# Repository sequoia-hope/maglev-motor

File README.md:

# Planar Maglev Motor Simulator

A browser-based design explorer and 6-DOF flight simulator for **moving-magnet
planar motors**: a Halbach permanent-magnet platen levitating over a stationary
array of ironless coils.

No build step, no dependencies. Serve the directory and open `index.html`:

```sh
python3 serve.py 8000           # then http://localhost:8000  (no-store headers; see the file)
```

It is also published as a static site from `main` by GitHub Pages:
<https://sequoia-hope.github.io/maglev-motor/>. Everything is relative paths and
pre-rendered files, so the Pages copy has every tab and both link-outs: the **Board
report** (`route/report/`) and **Pcbview** (copper, 3D and parts in `route/pcbview/`,
built from `route/pcbview.toml`).

Tests (Node 18+, no dependencies):

```sh
cd test && node physics.test.mjs && node flight.test.mjs && node optimise.test.mjs
```

---

## What it models

The whole machine reduces to one object: a **6×N wrench matrix** `W`.

```
[Fx Fy Fz Tx Ty Tz]ᵀ  =  W(pose) · i
```

Column *j* is the force and torque produced by one ampere in coil *j*. Because
that relationship is exactly linear, everything else falls out of it:

| Question | Answer |
|---|---|
| What currents do I command? | `i = W⁺w` — damped least-norm commutation |
| How much force can it make? | singular values of `W` |
| Are there dead spots? | poses where σ<sub>min</sub>(`W`) collapses |
| How hot does it get? | `Σ iⱼ²Rⱼ` |
| Will it fly? | integrate a rigid body driven by `W·i` |
| How few amplifiers can I get away with? | `W_eff = W·G` for a grouping `G` |
| What should I actually build? | constrained search over the coupled design space |

### The field model

The platen magnetisation is expanded as a 2-D Fourier series over one spatial
period. For each harmonic with in-plane wavevector **k**, the field below a slab
of thickness *D* is

```
Bz(k) = ½(1 − e^(−kD)) · [ M̂z − i(kx·M̂x + ky·M̂y)/k ] · e^(−kd)
Bx(k) = i(kx/k)·Bz(k)        By(k) = i(ky/k)·Bz(k)
```

with magnetisation in tesla (`|m| = Br`). The bracket **vanishes for the
wrong-handed harmonic** — the Halbach one-sided-flux condition is a consequence
of the algebra, not an assumption. `orientStrongSideDown()` measures which face
the flux exits and flips the array if needed, so new patterns can't be silently
built upside-down.

The exact Fourier coefficient of the piecewise-constant magnet cells carries a
sinc factor, which is where the classic discrete-Halbach amplitude penalty
`sin(π/M)/(π/M)` comes from — it is derived, not hardcoded.

Force and torque come from Lorentz integration of `I·dl × B` over every coil
filament, negated by Newton's third law.

### Phase grouping

Real machines do not give every coil its own current source. Coils are wired or
switched into a few phase groups and commutated against the magnet phase —
Zhu/Teo/Pang drive ~120 live coils from **eight** amplifiers. Model it as a
linear map `i = G·u` from phase currents to coil currents, and the wrench matrix
simply composes:

```
w = W·i = (W·G)·u
```

so allocation, singular values and dead-spot maps all work on `W_eff` unchanged
(`test/physics.test.mjs` checks `W_eff = W·G` is exact to 4e-16). `G` holds
sinusoidal commutation weights over spatial regions that subdivide each magnet
array and follow the platen — the physically realisable kind. What it costs:

| Preset | Drive | Amplifiers | Cond. | 6-DOF? | Hover | Tracking |
|---|---|---|---|---|---|---|
| PCB | independent | 144 | 2.6 | yes | 7.5 W | 42 µm |
| PCB | 2×2 per array | **16** | 5.6 | yes | 11.4 W | 42 µm |
| Wound (cross) | independent | 121 | 2.5 | yes | 38.6 W | 66 µm |
| Wound (cross) | 1 per array | **8** | 3.0 | yes | 72.8 W | 66 µm |
| Racetrack | independent | 108 | 6.2 | yes | 38.6 W | 206 µm |
| Racetrack | 3×3 per array | 36 | 20.4 | yes | 60.4 W | *worst-case lift 0.98×* |

The headline: **8 amplifiers track exactly as well as 121** on the four-array
cross, at roughly double the hover power. That is the published design, and the
model reproduces it. The racetrack is the exception — see limitations below.

### Reading the machine view

Every part is drawn as an extruded solid with its real thickness — magnet
stack, winding build height, backing plate — because those thicknesses *are*
the design. Two viewing aids, both of which distort the picture deliberately
and label themselves on the canvas when active:

- **Section cut** along x or y, with a draggable plane. Hides everything past
  the cut so you can see the layer stack and the air gap in cross-section.
- **Vertical exaggeration** (z×1–12). A 1.5 mm air gap under a 72 mm platen is
  otherwise a sub-pixel sliver.

The air gap carries a live dimension callout, since it is the variable
everything else trades against. The backing plate is drawn translucent so the
magnet array stays visible at true scale.

### The mechanical stack

Three numbers used to be invented: platen mass was `magnetMass × 1.6`, the
air-gap floor was `1.5% of platen size`, and cooling was a fixed
`h = 12 W/m²K`. `src/mechanical.js` replaces all three with parts that have a
material, a thickness and a manufacturing process.

**The air gap is now a tolerance stack**, not a guess:

```
gap_min = stator flatness + platen flatness + coil height variation
        + magnet thickness tolerance + thermal expansion
        + control error + safety margin
```

Every term is traceable. Flatness comes from the *process* — CNC ≈ 0.05 mm per
100 mm, PCB laminate ≈ 0.75% of diagonal per IPC-6012 — and it scales with part
size, so a bigger machine is a flatter machine only if you pay for it. On the
PCB preset, board flatness alone is 0.72 mm of a 1.32 mm floor: it is not a
contributor, it *is* the budget.

**The loop closes back on the simulator.** One term is the closed-loop control
error, which the flight sim measures. "Use measured error" on the Simulate tab
feeds the observed worst-case vertical excursion into the budget — because you
cannot fly closer to the stator than you can hold position. Quiet hover reads
sub-micron; kick the platen at 0.6 g and the peak excursion is **702 µm**,
which pushes the PCB preset's floor from 1.32 mm to **2.11 mm** — past the
1.5 mm gap it was designed around. Disturbance rejection and mechanical
clearance are the same budget, and this is the only way to see that.

It also prices things that were previously free. The magnet retainer wall
displaces 25% of the magnet layer on the PCB preset — that is field you do not
get — and adjacent Halbach magnets push about 15 N apart, which is what the
retainer wall has to survive during assembly.

### Design search

A 1-D sweep answers "what is the best pole pitch, holding everything else
fixed?" — the wrong question, because the optimum pitch depends on the air gap,
which depends on the winding height, which trades against turn count. The
**Optimise** tab searches them together: random sampling to find the basins, then
pattern search from the best candidates. ~330 designs/second, so a 500-design
search takes under two seconds and runs in animation frames without blocking.

Designs are **constrained, then ranked** — never a weighted sum of objectives. A
weighted sum silently trades a hard physical requirement for a soft one, and no
amount of low hover power compensates for a machine that cannot lift itself
somewhere in its workspace. Hard gates: worst-case lift, stator ΔT, current
density, amplifier count, full rank-6 controllability, and a buildable air-gap
floor. Then one objective (max acceleration, min power, max lift-per-watt, …).

Any result can be pushed back into the live config — from the best-design card,
a table row, or by clicking a point in the design-space scatter. Applying
**re-verifies at full solver quality**, since the search runs coarse; the two
agree to ~3%.

**Pin what you already know.** With ten coupled variables you usually know
several of them from the application — the platen has to be 120 mm, the gap has
to clear a 2 mm contamination budget — and want the budget spent on the rest.
Untick a dimension and it is held at the value shown, editable right there
(edits flow straight into the live design). Ticked dimensions get an editable
min/max, so you can also just narrow a range rather than pin it outright. The
panel reports how many of the variables are actually being searched.

Three things the search does that a sweep cannot:

- **Reports which bounds are binding.** If the winner sits on a search bound,
  the bound chose the value, not the physics, and it says so.
- **Reports why nothing was feasible.** A ranked histogram of which constraint
  blocked how many candidates — the top row is the one to loosen.
- **Shows the Pareto front**, so you can see the trade rather than just the
  single point that happened to win the objective you picked.

It also validates itself: given free rein over the coil-pitch ratio, the search
independently converges on **λ/3** — the three-phase spacing the literature
prescribes, and which this simulator earlier had to discover the hard way.

Run against the PCB preset it found, in ~350 designs, a machine strictly better
on every axis than the hand-tuned starting point:

| | hand-tuned | searched |
|---|---|---|
| Lift margin | 4.73× | **9.37×** |
| Lateral accel | 4.96 g | **6.8 g** |
| Hover power | 11.4 W | **4.71 W** |
| Stator ΔT | 51 K | **9.5 K** |
| Amplifiers | 16 | 16 |

### Validation

`test/physics.test.mjs` checks the model against independent ground truth:

- fundamental amplitude vs the closed form `Br(1−e^(−kD))·sin(π/M)/(π/M)`, for
  M = 2, 3, 4, 6, 8 — **exact to 0.00%**
- wrong-handed array's flux suppressed to 5×10⁻¹⁷ T
- field decay constant equals `2π/λ` to 1 part in 10⁶
- **lift capability of the assembled machine falls off at the harmonic decay
  rate** `k = 2π√2/λ` — an end-to-end check through geometry, Fourier
  decomposition, Lorentz integration and the allocator
- allocation linearity, pure-lift orthogonality, rank-6 controllability

The same fundamental check runs live in the sidebar. **If it says FAIL, nothing
else on screen is trustworthy.**

`test/flight.test.mjs` flies every preset through hover, circle and raster
trajectories and asserts it stays airborne and settles.

---

## Things the simulator taught us

These were found *by* the tool during development, and are the kind of thing it
exists to surface:

- **Coil pitch = λ/2 is a trap.** The coil grid lands exactly in phase with the
  magnet array and lateral force cancels *identically* at symmetric poses — a
  50× collapse in thrust while lift looks perfect. This is why three-phase
  designs use λ/3. The capability map shows it immediately.
- **Full-width racetrack coils cannot control yaw.** Force is uniform along each
  coil's length, so no current distribution produces T<sub>z</sub> and `W` drops
  to rank 5. Real racetrack stators are built as blocks of finite-length coils
  for exactly this reason.
- **There is an optimum pole pitch.** Run the pole-pitch sweep: lift margin
  peaks and hover power bottoms out at a specific λ for a given air gap. Too
  fine and the field never reaches the coils; too coarse and you waste magnet.
- **Saturation must prioritise levitation.** Scaling the whole commanded wrench
  back when the drivers run out throttles lift too, and the platen falls.
  `allocatePrioritised()` solves lift first and spends the remaining headroom on
  manoeuvring.
- **Turn count is not a free parameter.** Coil turns are derived from
  `(window area × 0.7) / wire area`. Allowing a turn count to be typed in
  produced a "12 mm" coil that would physically stand 96 mm tall and reported a
  lift margin it could never deliver — 56 kg of copper in a stator meant to lift
  1.7 kg.
- **Lift capability depends only on current density, not wire gauge.** Since
  turns × wire-area is fixed by the window, `lift ∝ N·I ∝ J`. Choosing thicker
  wire buys nothing but fewer turns. This is why the current-density tile, not
  the ampere limit, is the number that decides whether a design needs cooling.
- **Segmented racetrack coils need staggering.** Un-staggered, every coil in a
  column ends at the same y, so the platen periodically straddles a seam where
  only perpendicular end-turns sit beneath it. Lift collapsed to **0.16×
  weight** in bands a few mm wide — the platen fell straight through them.
  Staggering alternate columns by half a segment took worst-case lift from 0.16×
  to 1.44×.
- **Grouping is nearly free on the right layout, and impossible on the wrong
  one.** Eight amplifiers match 121 on the four-array cross; the racetrack loses
  so much capability that worst-case lift falls below 1× weight. Which topology
  you pick determines whether you need 8 drivers or 108.
- **A radial four-array cross has no yaw authority at all.** Each array at
  position `r` thrusting along `r` contributes `r × F = 0`. The arrays must
  thrust *tangentially*. This bug was invisible under per-coil control (single
  coils can still make yaw) and only surfaced once array-level grouping forced
  the layout's structure to matter — fixing it also improved independent-drive
  conditioning from 5.1 to 2.5.
- **Never judge a stator at its centred pose.** That pose is a symmetry point.
  `flight.test.mjs` now sweeps a ±30 mm workspace and demands the design hover
  *everywhere*; the racetrack dead bands were invisible to a centred check.

## Layout

```
index.html          Design (static analysis), Optimise (search), Simulate (flight)
src/math.js         vectors, quaternions, Cholesky, Jacobi eigenvalues
src/halbach.js      magnet tiles, Fourier decomposition, air-gap field
src/coils.js        stator topologies reduced to current filaments
src/physics.js      wrench matrix, allocation, rigid-body dynamics
src/control.js      6-DOF PID with gravity + acceleration feedforward, trajectories
src/analysis.js     design sweeps (gap, pole pitch, capability maps, ripple)
src/grouping.js     phase grouping: commutating many coils from few amplifiers
src/optimise.js     constrained multi-dimensional design search
src/mechanical.js   stack-up: masses, tolerance budget, thermal path
src/render3d.js     dependency-free solid-geometry 3-D canvas renderer
src/plots.js        line charts, heatmaps, bar strips with hover readouts
src/app.js          parameter UI, presets, the frame loop
```

## Known approximations

- **Finite array edges** use a half-pitch smooth taper on the periodic field.
  Errors are largest within about one pole pitch of an array edge; a truly
  finite array needs a surface-charge model.
- **No eddy currents, no iron, no back-EMF limit.** The current source is ideal;
  real drivers run out of voltage at speed.
- **Thermal estimate is crude** — a fixed natural-convection coefficient over
  the stator footprint. It flags designs that will obviously melt; it does not
  size a heatsink.
- **Magnet μ<sub>r</sub> = 1** (real NdFeB ≈ 1.05).
- **Winding packing is a flat 0.7**, reasonable for layer winding, optimistic
  for a hand-wound scramble winding (~0.5).
- **Commutation weights are sampled at each coil's centre.** Accurate for
  compact coils (square, PCB spiral), poor for long racetracks whose two long
  sides span a wide range of magnet phase. Some of the racetrack's poor
  behaviour under grouping is this approximation rather than the topology.
- **The search optimises the model, not reality.** Every approximation above is
  inherited, and an optimiser is extremely good at finding whichever corner of
  the model is least faithful. Treat a searched design as a hypothesis to check,
  not an answer — and read the active-bounds warning first.
- **Plate stiffness is not modelled.** Flatness comes from the manufacturing
  process, not from a deflection calculation, so a platen that is too thin to
  hold its own shape will not be caught.
- **Magnet-to-magnet force is an order-of-magnitude bound** (`B²/2µ₀` over the
  facing area). Real Halbach neighbours meet at 90°, so the load is largely
  shear and the true figure is lower.
- **No driver electrical model.** Amplifier count is reported, but voltage
  limits, back-EMF and the switching matrix itself are not simulated.
- The wrench matrix is rebuilt at the control rate, not every dynamics substep.

## Source literature

- W.-J. Kim, *High-Precision Planar Magnetic Levitation*, PhD thesis, MIT, 1997 —
  [dspace.mit.edu](https://dspace.mit.edu/handle/1721.1/10419). Where the field
  started: four Halbach linear levitation motors under one 5 kg platen.
- J. W. Jansen, *Magnetically Levitated Planar Actuator with Moving Magnets*,
  PhD thesis, TU Eindhoven, 2007 —
  [PDF](https://pure.tue.nl/ws/files/2471953/200711951.pdf). The harmonic
  force/torque model implemented here, plus commutation and decoupling.
- H. Zhu, T. J. Teo, C. K. Pang, *Design and Modeling of a Six-Degree-of-Freedom
  Magnetically Levitated Positioner Using Square Coils and 1-D Halbach Arrays*,
  IEEE Trans. Industrial Electronics 64(1):440–450, 2017 —
  [PDF](https://danielteodesigntechnology.wordpress.com/wp-content/uploads/2011/06/maglev_square_coils_tie2016.pdf).
  The most buildable topology.
- *Force and Torque Model of a Magnetically Levitated System with 2D Halbach
  Array and PCB Coils*, Sensors 23(21), 2023 —
  [open access](https://www.mdpi.com/1424-8220/23/21/8735). Tileable 16-layer
  PCB stator.
- *FleXstage*, arXiv 2309.11735 — [PDF](https://arxiv.org/pdf/2309.11735).
  Over-actuated lightweight platen.
- R. Chen, *A New Type of Magnet Array for Planar Motor*, MSc, UBC —
  [PDF](https://open.library.ubc.ca/media/stream/pdf/24/1.0340572/3). Array
  topologies with gaps and staggers.

Commercially this is [Planar Motor Inc.](https://planarmotor.com/) (UBC spinout)
and Beckhoff XPlanar — both moving-magnet 2-D Halbach over coil tiles.

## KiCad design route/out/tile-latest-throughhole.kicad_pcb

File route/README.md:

# Routing the amzhex coil board

A toolchain that takes the `amzhex` preset from the simulator to a real,
autorouted `.kicad_pcb` and checks it against JLCPCB's published 12-layer
capabilities. Everything here is a thin driver around `src/kicad.js` — the board
itself is still generated by the same code the app and the tests use.

```
gen.mjs      preset  ->  amzhex.kicad_pcb        (the real 12-layer board)
route.mjs    board   ->  amzhex.route.dsn        (the routing problem, see below)
freerouting  dsn     ->  amzhex.route.ses
finish.sh    ses     ->  out/*.kicad_pcb + DRC + PNG
```

Every step is reproducible from the one before it, and that is a property worth
keeping: `gen.mjs` rebuilds `amzhex.kicad_pcb` byte for byte from the preset,
and `finish.sh` rebuilds both boards in `out/` from that board plus the `.ses`.
The two things that once broke it — a net deleted by hand after the merge, and
the unrouted companion copied into `out/` by hand — are both steps now.

Run it:

```sh
node gen.mjs amzhex                                  # writes amzhex.kicad_pcb
node route.mjs amzhex amzhex.kicad_pcb               # writes amzhex.route.dsn
java -Xmx16g -jar freerouting-2.2.4.jar \
     -de amzhex.route.dsn -do amzhex.route.ses -mp 60
./finish.sh amzhex.kicad_pcb amzhex.route.ses amzhex-routed
```

`--tile=3` on `route.mjs` (with `SPARE=n gentile.mjs`) does the same on a 3x3
board, which is how everything here was debugged.

## Why the router does not see the real board

The full board is ~250 000 track segments of coil spiral. Handed that, freerouting
spends all its time re-deriving that none of it is routable, and one autorouter
pass on a NINE-coil tile took 86 seconds. It is also the wrong description of the
problem: the ten winding layers are not a routing resource, they are ten solid
layers of copper whose only effect on the router is that a plated THROUGH via
cannot be drilled through them.

So `mkdsn.mjs` writes the routing problem rather than the board:

* only the electronics (spare) layers exist, as signal layers;
* every coil is one hexagonal **via_keepout** — vias may not be drilled into the
  winding, which leaves exactly the gutter lattice, which is the physical truth;
* every crossover via, every terminal via and every crossover *tab* is a keepout
  too (see the notes below — each of those was learned the hard way);
* every pad is a single-pin component placed at its absolute position with its
  rotation baked into a polygon padstack, so no image/rotation/mirror convention
  can go wrong between the board and the router.

Same tile, same nets: 86 s/pass became 2 s/pass.

`mkses.mjs` merges the `.ses` back onto the FULL twelve-layer board, and that
merged board is what gets DRC'd. DRC on the proxy would prove nothing.

It also refuses to merge copper the router gave to two nets at once. freerouting
can return a session where one run belongs to two nets — round 2 of the amzhex
grind handed back 17 segments that were both `PWMA_92` and `VLOGIC`, identical
endpoints and opposite direction, plus collinear runs overlapping only in part.
Merged as given that is a dead short. `sharedCopper()` buckets every segment by
the infinite line it lies on and looks for overlapping extents from different
nets, which is linear rather than a 77-million-pair sweep and exact for this
failure mode. Where two nets share a run the one with *less* routing loses all
of it, copper and vias, and goes back to the ratsnest where it is visible as an
unrouted connection — dropping `VLOGIC` to save one coil's PWM would be the
wrong trade. The drop is printed, and what survives is re-checked rather than
assumed. This was first done by deleting the net by hand, which left the
published board unreproducible from its own inputs; it is now a step.

## Design rules

`fabRuleFiles()` in `src/kicad.js` generates the `.kicad_dru` and `.kicad_pro` that go
beside every exported board, from JLCPCB's published numbers
for FR-4 at 12 layers, 1 oz (read 2026-07-27):

| rule | value | source |
|---|---|---|
| min track / space | 0.09 / 0.09 mm | "1oz: 0.09/0.09mm (3.5/3.5 mil) for multi-layer" |
| min via hole / diameter | 0.15 / 0.25 mm | "Min. Via hole size/diameter" |
| min annular ring | 0.13 mm | JLCPCB support answer 110 |
| via hole-to-hole | 0.2 mm | "Via Hole-to-Hole Spacing" |
| copper to routed edge | 0.2 mm | "Copper clearance from routed board edges" |
| hole to copper | 0.2 mm | "Inner layer via hole to copper" |
| plated-hole aspect ratio | 8:1 | drill vs pressed board thickness |

They come out of the same `FAB` object the geometry is sized from, so the thing
being checked and the thing being drawn cannot drift.

The aspect ratio is the odd one out: it is the only fab limit that depends on
the **stack** rather than on the copper, so `fabRuleFiles()` takes the pressed
thickness and every via number falls out of it.

| stack | thickness | drill | ring on a 0.5 mm land |
|---|---|---|---|
| 12 layer, 1 oz | 1.570 mm | 0.20 mm (7.9:1) | 0.150 mm |
| 14 layer, 1 oz | 1.840 mm | 0.23 mm (8.0:1) | 0.135 mm |

KiCad has no aspect-ratio constraint, so the `.dru` states the drill *floor*
the ratio implies — a ratio the rule file cannot express is a ratio nothing
checks. That silence is exactly how the 14-layer board once shipped 698 routed
vias at 9.2:1 while DRC reported zero errors: every rule was a diameter.
`redrill.mjs` checks any existing board against its own stated thickness.

## Things that were wrong with the board, and are not now

Each of these was found by putting the board through this pipeline. Two of them
are shorts that **no PCB design-rule check can report**, because both halves of
the short are the coil's own net.

1. **Duplicate reference designators.** The dead-man's hold capacitor was `C1`,
   the same as coil 1's decoupling cap. KiCad's Specctra exporter keys its
   component list by reference and simply refuses to write the file — the board
   could not reach an autorouter at all. (`emitDeadman`, now `CDM1`/`RDM1`/etc.)

2. **A via no fab will drill.** The via was `min(0.4, max(0.2, pitch*0.6))`, a
   formula with no fab behind it, which came out 0.2 mm on a 0.1 mm drill and
   broke three JLCPCB rules at once — diameter, drill and annular ring. It is
   now derived from `FAB` and from the gutter the coil fill leaves
   (`viaSize`, `gutterFits`).

3. **A coil fill too greedy to host that via.** 84% fill leaves 0.59 mm of
   gutter; a legal via needs 0.79 mm (clearance in, via, edge clearance out).
   amzhex is now 80%, which costs *no* winding at all — turns-per-layer is
   `floor()`-quantised and comes out 12 either way.

4. **Odd winding-layer counts short every coil.** A spiral alternates which end
   it finishes on: layer 0 starts outside, layer 1 starts inside, and so on. With
   an ODD winding count the last layer ends in the CENTRE HOLE, and the tab that
   carries that lead out to its I/O pad crosses every turn of its own layer — a
   dead short of the whole layer, on all 168 coils. `pcbSpareLayers: 1`
   guarantees it. amzhex is now `2`. `validatePcb` checks it and
   `buildKiCad().stats.sameNetShorts` reports it.

5. **Via lands touching.** With a fab-sized via the five inner crossover vias
   nearly overlap in the centre hole. Same net, so DRC says nothing — but two
   touching lands weld the layer c/c+1 crossover to the c+2/c+3 one and short two
   whole layers out of the series stack. Now spread on a ring, and checked.

6. **`((a - b + PI) % 2PI) - PI`.** JS `%` is a remainder and keeps its sign, so
   this "smallest angle between two directions" returned garbage for half its
   inputs. It picked the hexagon flat 83 degrees away from a winding end, and the
   5.2 mm tangential tab that produced swept across the gutter and shorted a
   routed net to a coil. Now `atan2(sin(a-b), cos(a-b))`.

7. **A register placed on top of other parts.** The register search gave up after
   two cells and emitted the part on its target anyway; on the full board that
   put SR40's pads through U162's — six shorted nets. It now escalates its search
   radius the way the service parts always did.

8. **Both coil ends carried one net.** The winding is continuous copper, so its
   two terminals genuinely ARE one net and KiCad is right to say so — but the
   bridge's two outputs were given that same net, and a router reads the netlist,
   not the physics. Told that four pads are one net it satisfied it the cheap
   way: a wire straight from OUTA to OUTB. Every bridge output shorted, every
   coil bypassed, and the result reported as routed. The router is now handed
   the coil as a two-terminal COMPONENT (`coil_i_A` / `coil_i_B`, split in
   `route.mjs`) with the winding absent from its netlist; the pairing is the
   fixed convention `BRIDGE_OUT_PADS` records, so IN1 high always means current
   IN→OUT and the commutation signs mean the same thing on every cell.

9. **The bridge's exposed pad could not be connected to anything.** Chasing why
   GND kept failing turned up ratsnest entries reading *U1 ↔ U1*: the package's
   own power pads could not reach each other. A WSON/DFN die pad is an island —
   0.1 mm to all eight perimeter pads, which no legal trace fits through — and
   the usual escape, a via in the pad, is unavailable here because the part sits
   over winding copper, where a plated through hole would short the coil. The
   bridge is now a **SOT-23-6**: six perimeter pins is exactly an H-bridge's pin
   count, 0.95 mm pitch leaves 0.35 mm between pads (a 0.1 mm trace with
   clearance either side), and every pin is reachable. Packages with a
   `padIsland` now carry a large penalty in the fit search, because "fits best"
   and "can be wired" are different questions and the second one decides.

Plus, on the router side: pads were being mirrored (rotation applied in the
y-down frame and then y-flipped), which made every net touching a 30-degree
register unroutable; keepouts have to be grown by a clearance because
freerouting does not apply the clearance rule to them; and terminal vias need
keepouts on the inner electronics layers even though their B.Cu land is a pad.

## The stack: 12 + 2, not 12

The electronics layers are ADDED to the twelve winding layers rather than taken
out of them, so the board is 14 copper layers. Both halves matter:

* they must come in a **pair**, because an odd winding count strands a coil lead
  in the centre hole (finding 4 above);
* they must be **added**, because taking two out of twelve costs a fifth of the
  winding — 120 turns instead of 144 — and buys no routing improvement at all
  (measured on the 3x3 tile: 12+2 and 14+2 both plateau within two connections
  of each other).

The price is a 14-layer stack, which is past the layer count where PCB pricing
turns steep, and a wider via drill: 1.84 mm of board through a 0.2 mm hole is a
9:1 plated hole and the fab does 8:1, so `minDrillFor()` opens it to 0.23 mm and
the ring comes down to 0.135 mm — still over the 0.13 mm floor.

## Known remaining

* **GND and VBUS want to be planes, not nets.** 749 and 505 pads respectively.
  `PLANES=GND,VBUS` keeps them out of the router's netlist for experiments; a
  real build should surrender two more layers to a GND and a VBUS pour (which
  keeps the winding count even, so parity stays satisfied) and let the router
  have only the signals.
* **Freerouting plateaus at roughly half the board, and nothing moves it.**
  It converges and then stops -- a 150-pass run on the 3x3 tile finished in the
  same 2 minutes and at the same 44 unrouted as a 30-pass one. Everything tried,
  measured on that tile (unrouted connections, lower is better):

  | change | result |
  |---|---|
  | 2 electronics layers | 42-44 |
  | 4 electronics layers | 44 |
  | 6 electronics layers | 44 |
  | 30 passes vs 150 passes | identical |
  | register quads: 4-in-a-row vs 2x2 block | 44 -> 42 |
  | GND/VBUS routed vs excluded (i.e. poured) | 37 vs 34 signal connections |
  | local nets pre-laid as fixed wiring | 5x slower, no further |

  **A trap worth knowing:** freerouting 2.2.4 silently IGNORES a
  `freerouting.json` in the working directory. Setting `max_passes: 1` there
  runs 24 passes; the same setting as `FREEROUTING__ROUTER__MAX_PASSES=1` runs
  one. Every router setting has to go through those `FREEROUTING__`-prefixed
  environment variables (double underscore per level of nesting), and until
  that was found none of the tuning above was reaching the router at all. With
  it reaching the router, `VIA_COSTS=10 START_RIPUP_COSTS=1000` is the best
  combination found -- worth 42 -> 38, and it does change behaviour (via count
  goes 17 -> 29 as the cost drops), but it does not change the conclusion.

  Later measurements, same tile, through-hole vias only:

  | change | result |
  |---|---|
  | gutter vias per cell 7 -> 4 (fewer winding layers) | 38 -> 37 |
  | coil fill 0.80 -> 0.74 -> 0.68 (wider gutter, smaller coil) | 38 -> 40 -> 38 |
  | coil centre hole enlarged (144 -> 132 -> 108 turns) | 45 -> 46 -> 43 |
  | **blind vias between the two electronics layers** | **38 -> 5** |

  The full 168-coil board does NOT converge the way the tile does -- it keeps
  gaining: 1245, 1193, 1125, 1073, 1002, 933, 877, 835, 778, 771, 710 unrouted
  over eleven passes. Note the tenth pass (778 -> 771, a gain of 7) followed by
  the eleventh (771 -> 710, a gain of 61): a single slow pass is NOT convergence
  on this board, and reading it as one is a mistake worth not repeating. Hence
  grind.sh, which keeps going in rounds and carries each round's result forward
  rather than stopping at a fixed pass count.

  So it is not the gutter being crowded (halving its via count moved one
  connection), not the gutter being narrow (a wider one costing 12 turns moved
  nothing), and not the coil's centre hole (36 turns bought nothing). The only
  thing that moves it is where a via may be PLACED. With plated through-holes a
  via can only go where no winding layer has copper -- the gutter lattice, plus
  a centre hole too small to use -- so inside a cell, under the parts, B.Cu is
  the only layer a trace can reach. That is why extra electronics layers are
  worthless: they are all equally unreachable. Allow a blind via between the two
  electronics layers, which never enters the winding, and the same tile goes
  from 38 unrouted to 5 (19 vias placed becomes 116). That is a fabrication
  decision, not a layout one.

  More layers do not help; more passes do not help; taking the power nets out
  does not help the signals. What IS routed comes back DRC-clean every time, so
  this is the router giving up rather than the board being full -- the rendered
  result still has a lot of empty copper. A different autorouter, or a
  purpose-built one that exploits the lattice's periodicity, is the next thing
  to try.
* **The square-grid presets (`pcb`, `pcbmini`, `pcb2oz`) are still at 0.94 fill**,
  which leaves 0.24 mm of gutter — not enough for a fab-legal via. They export,
  and `gutterFits()` reports the shortfall, but their vias are pinned against the
  winding. Fixing them means the same fill reduction, which for them *does* cost
  turns (13 -> 11), so it is a design decision rather than a bug fix.

## The full board: tile what tiles, route the rest in place (2026-10)

`./full.sh` produces the whole 12x14 board routed end to end — every register,
bridge, coil lead, bus and the 42-register shift chain — and `./fullgate.sh`
checks it with no exemptions. Page: `report/index.html`.

```
stamp2.mjs    bare board -> the 2x2 quad stamp, routed on a TORUS       (t2gate.sh)
service.mjs   bare board -> + header and dead-man, placed before routing
assemble.mjs  stamp + board -> pattern, patch the rim, board-level nets  (fullgate.sh)
```

**Why not just clone the stamp.** Cloning was what `quadclone.mjs` did, and its
gate (`hand.sh check`) skipped everything within 6 mm of the outline as "spine
territory". Measured per quad with pcbnew, only the 20 interior quads take the
stamp whole; all 22 rim quads break — copper trimmed at the outline in the south
band, bridges and caps rotated off the cut by `quadgen`'s `fitOrNudge` in the
north band and east column, and no bus ladder at the west and east edges. Do not
use `quadclone.mjs` or `hand.sh`'s clone gate to judge a board.

**`gridrouter.mjs`** is a negotiated-congestion (PathFinder) router on a 0.025 mm
grid over all 14 copper layers. Static copper is rasterised from the real
primitives with exact distance, so a node is legal iff a track centred there
clears every foreign edge; routed nets claim discs (track–track 0.19, track–via
0.39, via–via 0.59 mm) and are ripped up and re-routed until nobody shares a
cell. `wrap: true` makes the grid a torus.

**`stamp2.mjs`** takes ONE lattice period of the bare board and routes the
quad's 24 nets at once. Because the period wraps, a net's copper and every
periodic image of every other net are the same cells: tiling is the topology of
the search, not a check afterwards. Per-quad nets get a window narrower than a
period, so a net can never meet its own image. The straight In12 lanes and power
trunks come from `fabtile2.union.ses` as fixed copper. `MESH=2` links each bus
net's lane rows north–south inside the stamp (no margin spines needed);
`RESERVE` keeps two clean east–west In12 lines empty for the chain returns.

**`assemble.mjs`** works on one board-wide grid that the stamp's grid is a period
of. It lays a stamp path on a quad only if every node is legal against that
quad's real copper and both ends are anchored (dropped whole otherwise), then
asks each quad what its pins still need and routes exactly that in a window of
the real board. A quad that will not settle has its own patterned paths ripped
up and is routed from scratch, together with whatever that opens in finished
neighbours. Connectivity is "same-class copper sharing a grid node"; it has
matched pcbnew's ratsnest count exactly on every board so far.

Things that cost time, in the order they bit:

- A routed net's own claim is in the occupancy counts — take it out before
  asking whether the net is in conflict, or every net fights itself forever.
- History has to go on the whole contested disc, not the centreline nodes, and
  the present-sharing factor must be capped; otherwise the same four nets swap
  one corridor for a hundred iterations.
- Winding corner fillets are ~1 mm-radius arcs. Tessellate them to < 0.5 um
  sagitta, or copper routed along a fillet sits microns inside the clearance
  (KiCad found it; the model had not).
- The constructed lanes are zero-margin by design. Validate them on their true
  centreline; grid nodes 0.6 h off it fail the same test.
- `hole_to_hole` is a *warning* in the generated project file. Two same-net
  vias 0.075 mm apart went through an errors-only gate; `fullgate.sh` now counts
  it, and the router keeps a net's own new vias apart.
- The header fits in exactly four places at >= 0.2 mm from every barrel. One
  walls a bridge pad in; the interior one leaves the header's DATA pins no path
  to their lanes even with its quad routed from scratch; the east-rim one
  routes. Placement is route-tested, not clearance-tested.
- A long net laid first walls pins in (SR.12 on the west edge: "target walled in:
  284 nodes"); a rim patch laid first walls the long net's pin in. So the chain
  ends arrive on the reserved lanes, and the last hop from lane to pin is one of
  the quad's own jobs, negotiated with everything else in that quad.
- Nothing is laid from a negotiation that did not converge: the copper that did
  settle is exactly what the leftovers cannot get past. Rip the quad's own
  patterned paths up and route it from scratch instead — with whatever that
  opens in finished neighbours, because a pad may be fed by the neighbour's
  image of a path.
- Long east–west nets cannot cross 100 mm of finished stamps on any layer. The
  stamp has to reserve the line; nothing downstream can find one.

## Power: rails in the gutters (2026-10)

Every bus lane on this board is a 0.1 mm track, VBUS and GND included, and no
wider lane fits. The first full board fed 168 bridges through that: the worst
bridge saw 786 mohm of supply loop, the GND pin reached the mesh through 6 mm of
one track and another bridge's pad, and at 3 A that track is a fuse.

What the board does have is the **gutter**: 1.7 mm between neighbouring
windings on all twelve winding layers, holding nothing but barrels. `pour.py`
pours GND on seven layers and VBUS on the other seven, alternating, with
KiCad's own zone filler against the board's own rule files (0.12 mm from
foreign copper; the fab minimum is 0.09), nothing over a coil face. Every power
barrel standing in a gutter ties its net's layers together. Tracks stay; the
pour is copper in parallel.

A poured honeycomb is a closed ring round every coil on every layer -- a
shorted turn coupled to a 144-turn winding switched at PWM frequency.
Estimated from the geometry (ring ~3 mohm, ~16 nH per net, coupling ~0.3) the
rings would turn 0.2-2 W of PWM ripple into heat at hover, against 5.6 W of
hover power and the few milliwatts the rail network itself dissipates. So the
pour is cut into a tree. The gutter lattice is a honeycomb graph (388
junctions, 555 flats); it is poured whole and solved with `powercheck.py`'s
network, the current the pour carries through each flat is read off, and the
rails are the maximum spanning tree of that -- the arteries the honeycomb was
already using. Every flat outside the tree gets one 0.2 mm slit: one per coil.
Which flats conduct is decided by the routed board (ladders, crossover farms,
links riding winding layers, two layers with no barrel between them), so it is
measured, not assumed; the slit flats carried 12% of the flat current. The
slits are rule areas in the board file, so a refill in KiCad reproduces the
tree. Earlier shapes -- east-west rails with a seam spine, north-south rails
with a zigzag spine -- were worse (248 and 262 mohm), because a seam's two
columns of ladder barrels leave a pour 0.19 mm of passage and a single spine
through them chokes.

Gates: `ringcheck.py` projects every poured polygon, all layers and both
nets, onto one plane and floods it from outside the board; every coil's
winding must be reachable. `powercheck.py` turns every VBUS/GND track, barrel,
pad and pour cell into a resistor network (1 oz copper, 20 um plating), feeds
it at the header pins and loads every bridge; it refuses to report if a bridge
pin is unreachable (a hole in the model, since the board has no open nets),
and the 0.05 mm raster agrees with the 0.1 mm one within 2%. DRC sees the
pour: a fill shifted 0.06 mm sideways returns 510 clearance errors.

Measured on `out/amzhex-full.kicad_pcb` (page: `report/index.html`, section 06):

| | tracks only | with the rails |
|---|---|---|
| supply loop per bridge, min / median / max | 195 / 477 / 786 mohm | 51 / 93 / 178 mohm |
| rail lost at the worst bridge, hover 0.62 A | 219 mV | 29 mV |
| same at 3 A | 1059 mV | 142 mV |
| VBUS, hardest-worked conductor at hover | 177 A/mm2 (all of it in one track) | 62 A/mm2 |
| GND, hardest-worked conductor at hover | 177 A/mm2 | 177 A/mm2 |

The GND line is the open item. The header's pads sit over a coil face, so the
only way into the board is a barrel in the nearest gutter; the router gave the
VBUS pin two barrels 0.1 mm away (a B.Cu pour now joins them properly), and
gave GND one 6 mm away through a track. `service.mjs` can place a pin's own
barrels and copper tabs BEFORE routing (`FEED_VIAS`), and that works
electrically (12-20 mV at hover, loop <= 150 mohm in every trial) -- but the
header quad does not survive it: six full route tests, six boards with 2-9
connections open (the record is in `service.mjs`). The quad with the header is
at the edge of routability, and a feed barrel takes a crossing slot its PWM
tracks need. So the feed wants a different header spot or pinout, which is a
design decision, and `powercheck.py`'s gate (70 A/mm2 at hover, the windings'
own density) stays red on GND until then. As built, GND's feed is good for
about hover (0.62 A in a 0.1 mm outer-layer track, ~20 K rise) and the
connector's own 1.27 mm pin is rated about the same.

## Pcbview (2026-10)

`pcbview.toml` → `~/Software/pcbview/bin/pcbview build route/pcbview.toml` → `pcbview/`:
every copper layer plotted by kicad-cli in board coordinates, the GLB of the board, and
the part pane with LCSC numbers, as a static site. The simulator links out to it
("Pcbview", beside "Board report") and GitHub Pages serves it unchanged. Rebuild after
the board changes; the layer plots are the heavy part.

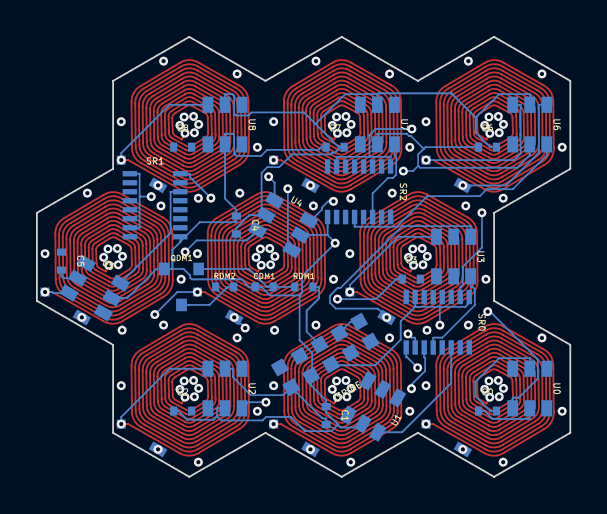
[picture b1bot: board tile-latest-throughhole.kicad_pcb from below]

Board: 14 copper layers, 29.6 x 24.4 mm, 44 parts (44 on the bottom side), 40 nets.

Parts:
C0, C1, C2, C3, C4, C5, C6, C7, C8: 100n; C0402
CDM1: hold; R0402
J0.IN, J0.OUT, J1.IN, J1.OUT, J2.IN, J2.OUT, J3.IN, J3.OUT, J4.IN, J4.OUT, J5.IN, J5.OUT, J6.IN, J6.OUT, J7.IN, J7.OUT, J8.IN, J8.OUT: term; Term
JSPINE: spine 2x5 1.27mm; HDR10
QDM1: dead-man; SOT23
RDM1: retrigger; R0402
RDM2: pull-up; R0402
SR0, SR1, SR2: 74HC595BQ; SR595Q
U0, U1, U2, U3, U4, U5, U6, U7, U8: TC118S-class; SOT23HB

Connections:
DATA_0: JSPINE.4, SR0.12
DATA_1: SR0.2, SR1.12
DATA_2: SR1.2, SR2.12
DATA_3: JSPINE.5, SR2.2
DEADMAN_G: CDM1.1, QDM1.1, RDM1.2
GND: C0.2, C1.2, C2.2, C3.2, C4.2, C5.2, C6.2, C7.2, C8.2, CDM1.2, JSPINE.2, QDM1.2, SR0.1, SR1.1, SR2.1, U0.3, U1.3, U2.3, U3.3, U4.3, U5.3, U6.3, U7.3, U8.3
OE_N: QDM1.3, RDM2.1, SR0.10, SR1.10, SR2.10
PWMA_0: SR0.14, U0.1
PWMA_1: SR0.13, U1.1
PWMA_2: SR1.14, U2.1
PWMA_3: SR0.9, U3.1
PWMA_4: SR0.5, U4.1
PWMA_5: SR1.13, U5.1
PWMA_6: SR2.9, U6.1
PWMA_7: SR2.13, U7.1
PWMA_8: SR2.14, U8.1
PWMB_0: SR0.15, U0.5
PWMB_1: SR0.11, U1.5
PWMB_2: SR1.15, U2.5
PWMB_3: SR0.7, U3.5
PWMB_4: SR0.3, U4.5
PWMB_5: SR1.11, U5.5
PWMB_6: SR2.7, U6.5
PWMB_7: SR2.11, U7.5
PWMB_8: SR2.15, U8.5
RCLK: JSPINE.7, SR0.8, SR1.8, SR2.8
SCL: JSPINE.9, JSPINE.10
SCLK: JSPINE.6, SR0.6, SR1.6, SR2.6
SYNC: JSPINE.8, RDM1.1
VBUS: C0.1, C1.1, C2.1, C3.1, C4.1, C5.1, C6.1, C7.1, C8.1, JSPINE.1, U0.4, U1.4, U2.4, U3.4, U4.4, U5.4, U6.4, U7.4, U8.4
VLOGIC: JSPINE.3, RDM2.2, SR0.4, SR0.16, SR1.4, SR1.16, SR2.4, SR2.16
coil_0: J0.IN.1, J0.OUT.1, U0.2, U0.6
coil_1: J1.IN.1, J1.OUT.1, U1.2, U1.6
coil_2: J2.IN.1, J2.OUT.1, U2.2, U2.6
coil_3: J3.IN.1, J3.OUT.1, U3.2, U3.6
coil_4: J4.IN.1, J4.OUT.1, U4.2, U4.6
coil_5: J5.IN.1, J5.OUT.1, U5.2, U5.6
coil_6: J6.IN.1, J6.OUT.1, U6.2, U6.6
coil_7: J7.IN.1, J7.OUT.1, U7.2, U7.6
coil_8: J8.IN.1, J8.OUT.1, U8.2, U8.6
